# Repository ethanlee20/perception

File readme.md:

<h1 align="center">

</h1>

Overview
-----------------------------

Codebase for the Swarm on a Stick - Perception group.

Includes code for:

- deployment 
- unit testing 
- subsystem testing
- calibration

Prototyping code written in micropython for use with ESP32 microcontroller.

Supported hardware
------------------
- ToF Sensor
- Servo motor
- Hall Effect Encoder
- IR sensor
- Piezo buzzer
- Microphone
- 9-axis IMU
- Gesture Sensor
- OLED display
- Button

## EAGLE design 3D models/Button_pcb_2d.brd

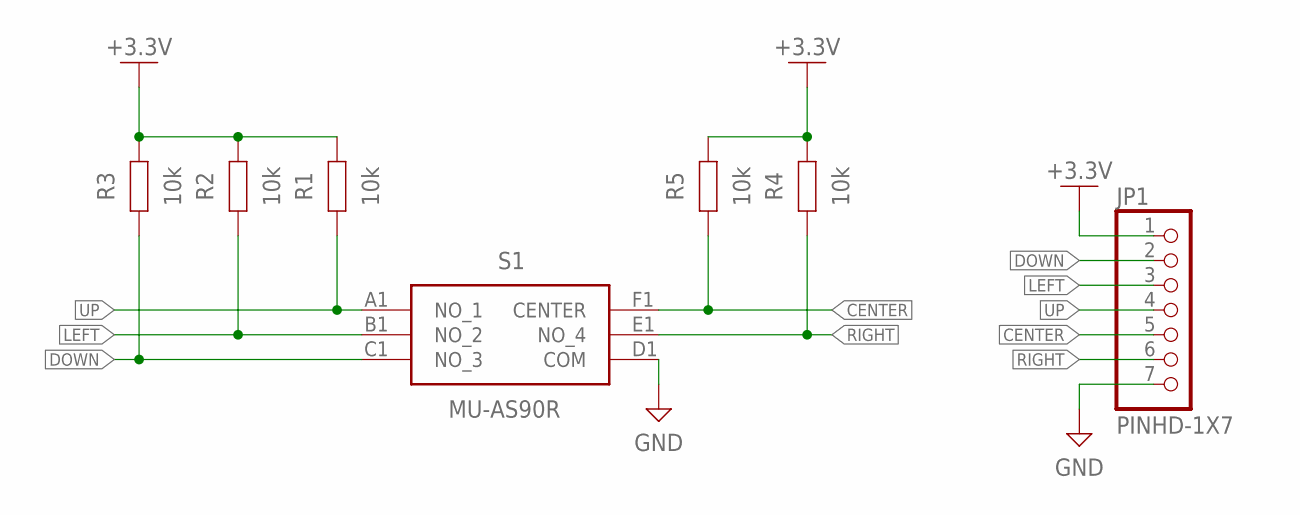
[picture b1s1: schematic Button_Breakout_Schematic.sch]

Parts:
JP1: PINHD-1X7; 1X07
R1, R2, R3, R4, R5: 10k; RESC1608X60
S1: MU-AS90R; MUAS90R

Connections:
+3.3V: JP1.1, R1.2, R2.2, R3.2, R4.2, R5.2
CENTER: JP1.5, R5.1, S1.F1 (CENTER)
DOWN: JP1.2, R3.1, S1.C1 (NO_3)
GND: JP1.7, S1.D1 (COM)
LEFT: JP1.3, R2.1, S1.B1 (NO_2)
RIGHT: JP1.6, R4.1, S1.E1 (NO_4)
UP: JP1.4, R1.1, S1.A1 (NO_1)

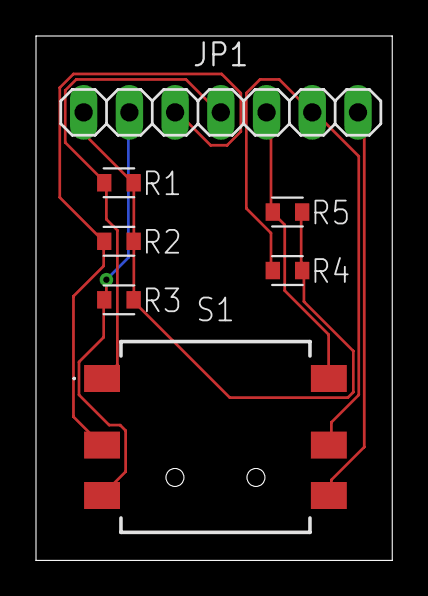
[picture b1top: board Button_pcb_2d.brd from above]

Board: 2 copper layers, 19.8 x 29.1 mm, 7 parts (0 on the bottom side), 7 nets.

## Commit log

2025-02-20 read me
2025-02-20 typo
2025-02-21 Rename perpection.png to perpection_2.png
2025-02-25 Added housing 3D model file
2025-02-25 simple test
2025-02-26 display and vec2d
2025-02-26 change
2025-03-03 added vl53l0x library and dependency
2025-03-04 oled display
2025-03-05 range viz and reorganize
2025-03-06 cpp translation in progress
2025-03-06 c++ range visualizer complete?
2025-03-07 fix includes
2025-03-07 neopixel
2025-03-07 subsystem integration
2025-03-07 cleanup
2025-03-08 moved python to misc
2025-03-08 use esp32 servo library
2025-03-08 const members in Range_Visualizer
2025-03-08 keep trying to connect to sensor
2025-03-08 taking test measurement is const
2025-03-08 VL53L0X wrapper inheritence to automatically expose adafruit library's public methods without explicit forwarding
2025-03-08 move circuitpy lib to misc
2025-03-08 debug tof sensor with inheritence
2025-03-08 separated source code from testing code
2025-03-08 main perception code in root folder
2025-03-08 fixed construction with const members in range_visualizer
2025-03-08 integration test updates
2025-03-08 updated gitignore
2025-03-08 servo uses inheritence
2025-03-09 rename servo file
2025-03-09 fix neopixel test case
2025-03-09 main perception.ino changes
2025-03-09 working piezo buzzer
2025-03-09 arduino uno lib test
2025-03-09 debug neopixel
2025-03-09 fix neopixel test
2025-03-09 added neopixel changes to perception code
2025-03-09 tof sensor continuous mode
2025-03-09 neopixel rotates colors non-blocking with millis instead of delay
2025-03-10 button
2025-03-10 button initialize in main
2025-03-10 display keep retrying to initialize instead of stall forever on first fail
2025-03-10 OLED is inherited
2025-03-10 debug perception
2025-03-10 menu on display
2025-03-10 range visualizer works with display. use enum for modes for clarity
2025-03-10 distinguish display mode and menu mode
2025-03-10 added correct toggling of button
2025-03-10 make enum namespaces so there's no conflict of members
2025-03-10 automate menu screen using enum of options
2025-03-10 increase debounce time for button
2025-03-10 play song non-blocking
2025-03-10 button test
2025-03-10 and his name is john cena
2025-03-11 added but commented out mic
2025-03-11 encoder code
2025-03-11 initialize piezo buzzer
2025-03-12 apply change of coordinate frame transformation
2025-03-17 added button pcb
2025-03-17 rename 3d models for button
